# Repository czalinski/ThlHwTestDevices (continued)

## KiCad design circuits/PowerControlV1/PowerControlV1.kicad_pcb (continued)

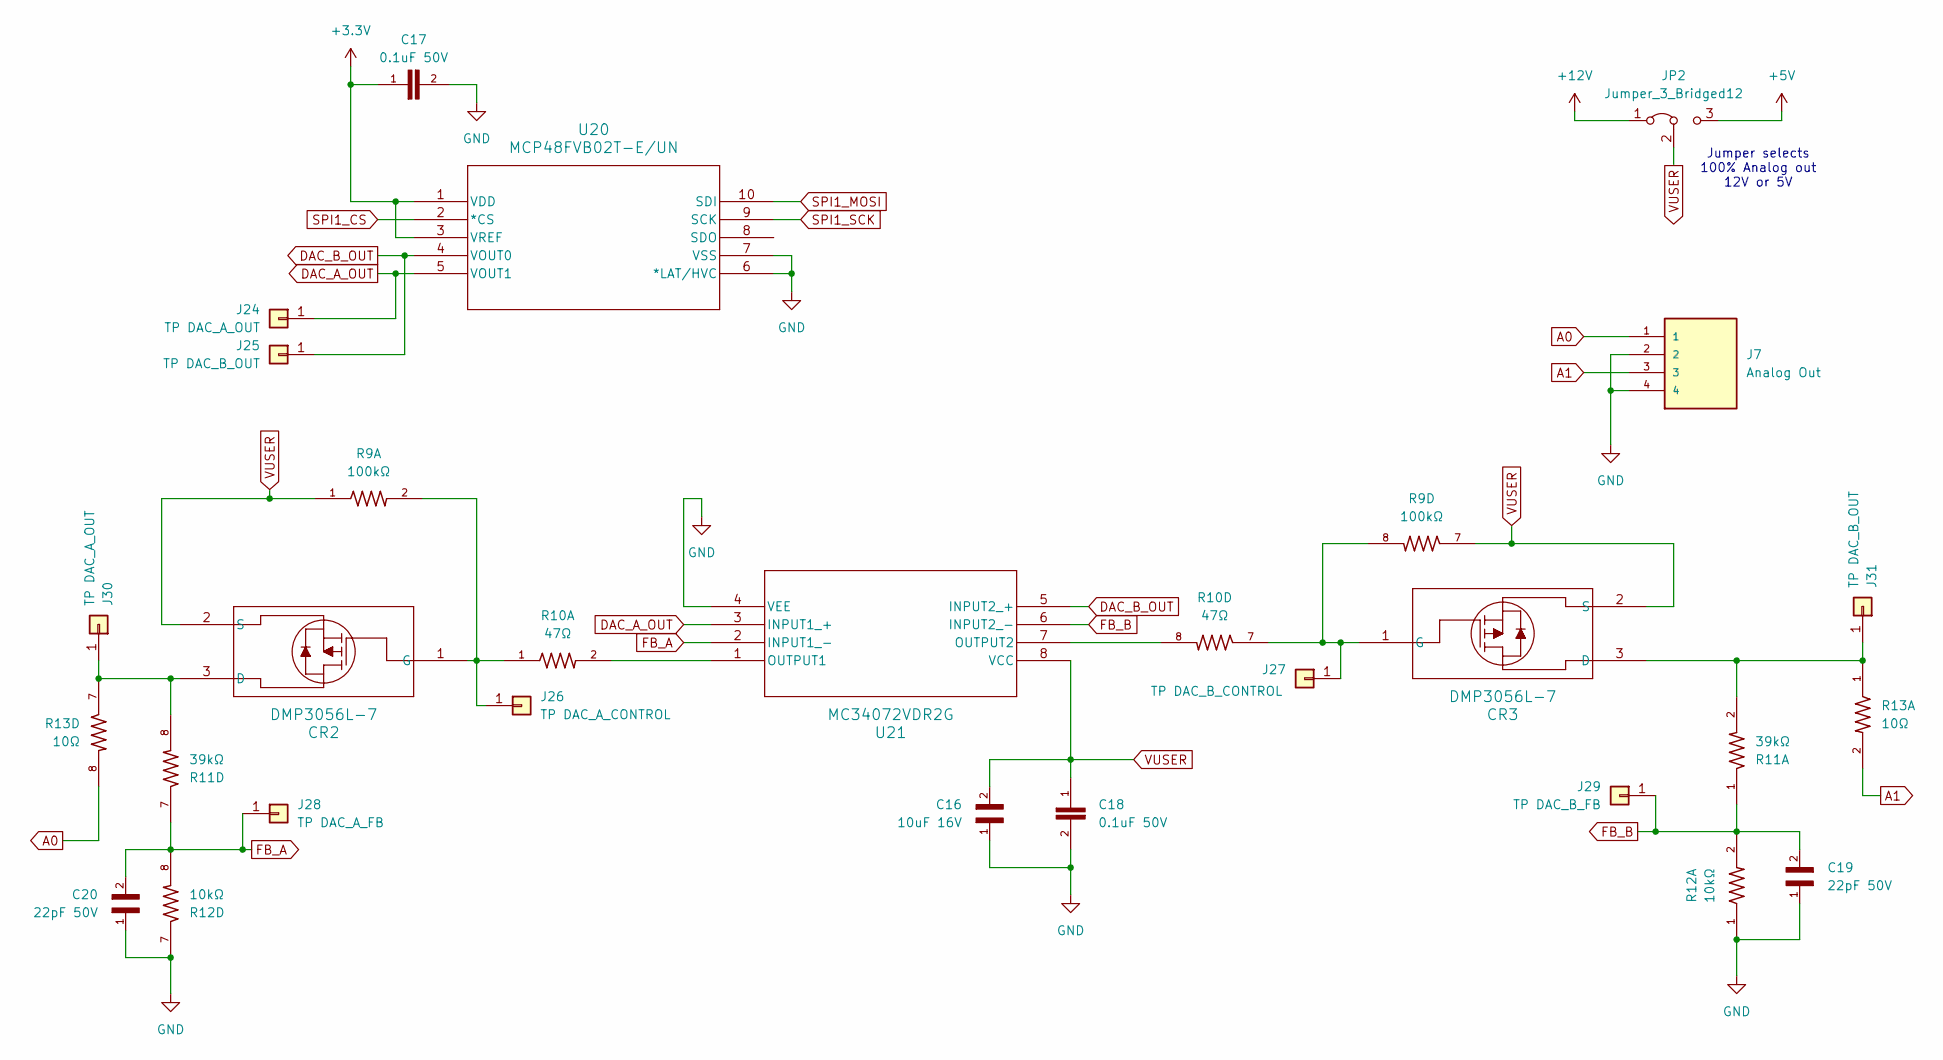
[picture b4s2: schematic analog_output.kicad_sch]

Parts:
C16: 10uF 16V; CAPC2012X140N
C17, C18: 0.1uF 50V; CAPC2012X70
C19, C20: 22pF 50V; CAPC1005X55N
CR2, CR3: DMP3056L-7; DIODE3_DESD1CAN2SOQ-7_DIO
J7: Analog Out; TE_1985218; PARTREV 29.03.2021
J24, J30: TP DAC_A_OUT; PinHeader_1x01_P2.54mm_Vertical
J25, J31: TP DAC_B_OUT; PinHeader_1x01_P2.54mm_Vertical
J26: TP DAC_A_CONTROL; PinHeader_1x01_P2.54mm_Vertical
J27: TP DAC_B_CONTROL; PinHeader_1x01_P2.54mm_Vertical
J28: TP DAC_A_FB; PinHeader_1x01_P2.54mm_Vertical
J29: TP DAC_B_FB; PinHeader_1x01_P2.54mm_Vertical
JP2: Jumper_3_Bridged12; PinHeader_1x03_P2.54mm_Vertical
R9: 100kΩ; RESCAV80P320X160X70-8N
R10: 47Ω; RESCAV80P320X160X70-8N
R11: 39kΩ; RESCAV80P320X160X70-8N
R12: 10kΩ; RESCAV80P320X160X70-8N
R13: 10Ω; RESCAV80P320X160X70-8N
U20: MCP48FVB02T-E/UN; MSOP10_UN_MCH
U21: MC34072VDR2G; SOIC8_ONS

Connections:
+3.3V: C17.1, U20.1 (VDD), U20.3 (VREF); also elsewhere on the board
+5V: JP2.3 (B); also elsewhere on the board
+12V: JP2.1 (A); also elsewhere on the board
A0: J7.1, R13.8
A1: J7.3, R13.2
DAC_A_OUT: J24.1, U20.5 (VOUT1), U21.3 (INPUT1_+)
DAC_B_OUT: J25.1, U20.4 (VOUT0), U21.5 (INPUT2_+)
FB_A: C20.2, J28.1, R11.7, R12.8, U21.2 (INPUT1_-)
FB_B: C19.2, J29.1, R11.1, R12.2, U21.6 (INPUT2_-)
GND: C16.1, C17.2, C18.2, C19.1, C20.1, J7.2, J7.4, R12.1, R12.7, U20.6 (*LAT/HVC), U20.7 (VSS), U21.4 (VEE); also elsewhere on the board
unnamed: CR2.3 (D), J30.1, R11.8, R13.7
unnamed: CR2.1 (G), J26.1, R9.2, R10.1
unnamed: CR3.3 (D), J31.1, R11.2, R13.1
unnamed: CR3.1 (G), J27.1, R9.8, R10.7
unnamed: R10.2, U21.1 (OUTPUT1)
unnamed: R10.8, U21.7 (OUTPUT2)
SPI1_CS: U20.2 (*CS); also elsewhere on the board
SPI1_MOSI: U20.10 (SDI); also elsewhere on the board
SPI1_SCK: U20.9 (SCK); also elsewhere on the board
VUSER: C16.2, C18.1, CR2.2 (S), CR3.2 (S), JP2.2 (C), R9.1, R9.7, U21.8 (VCC)

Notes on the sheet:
Jumper selects 100% Analog out 12V or 5V

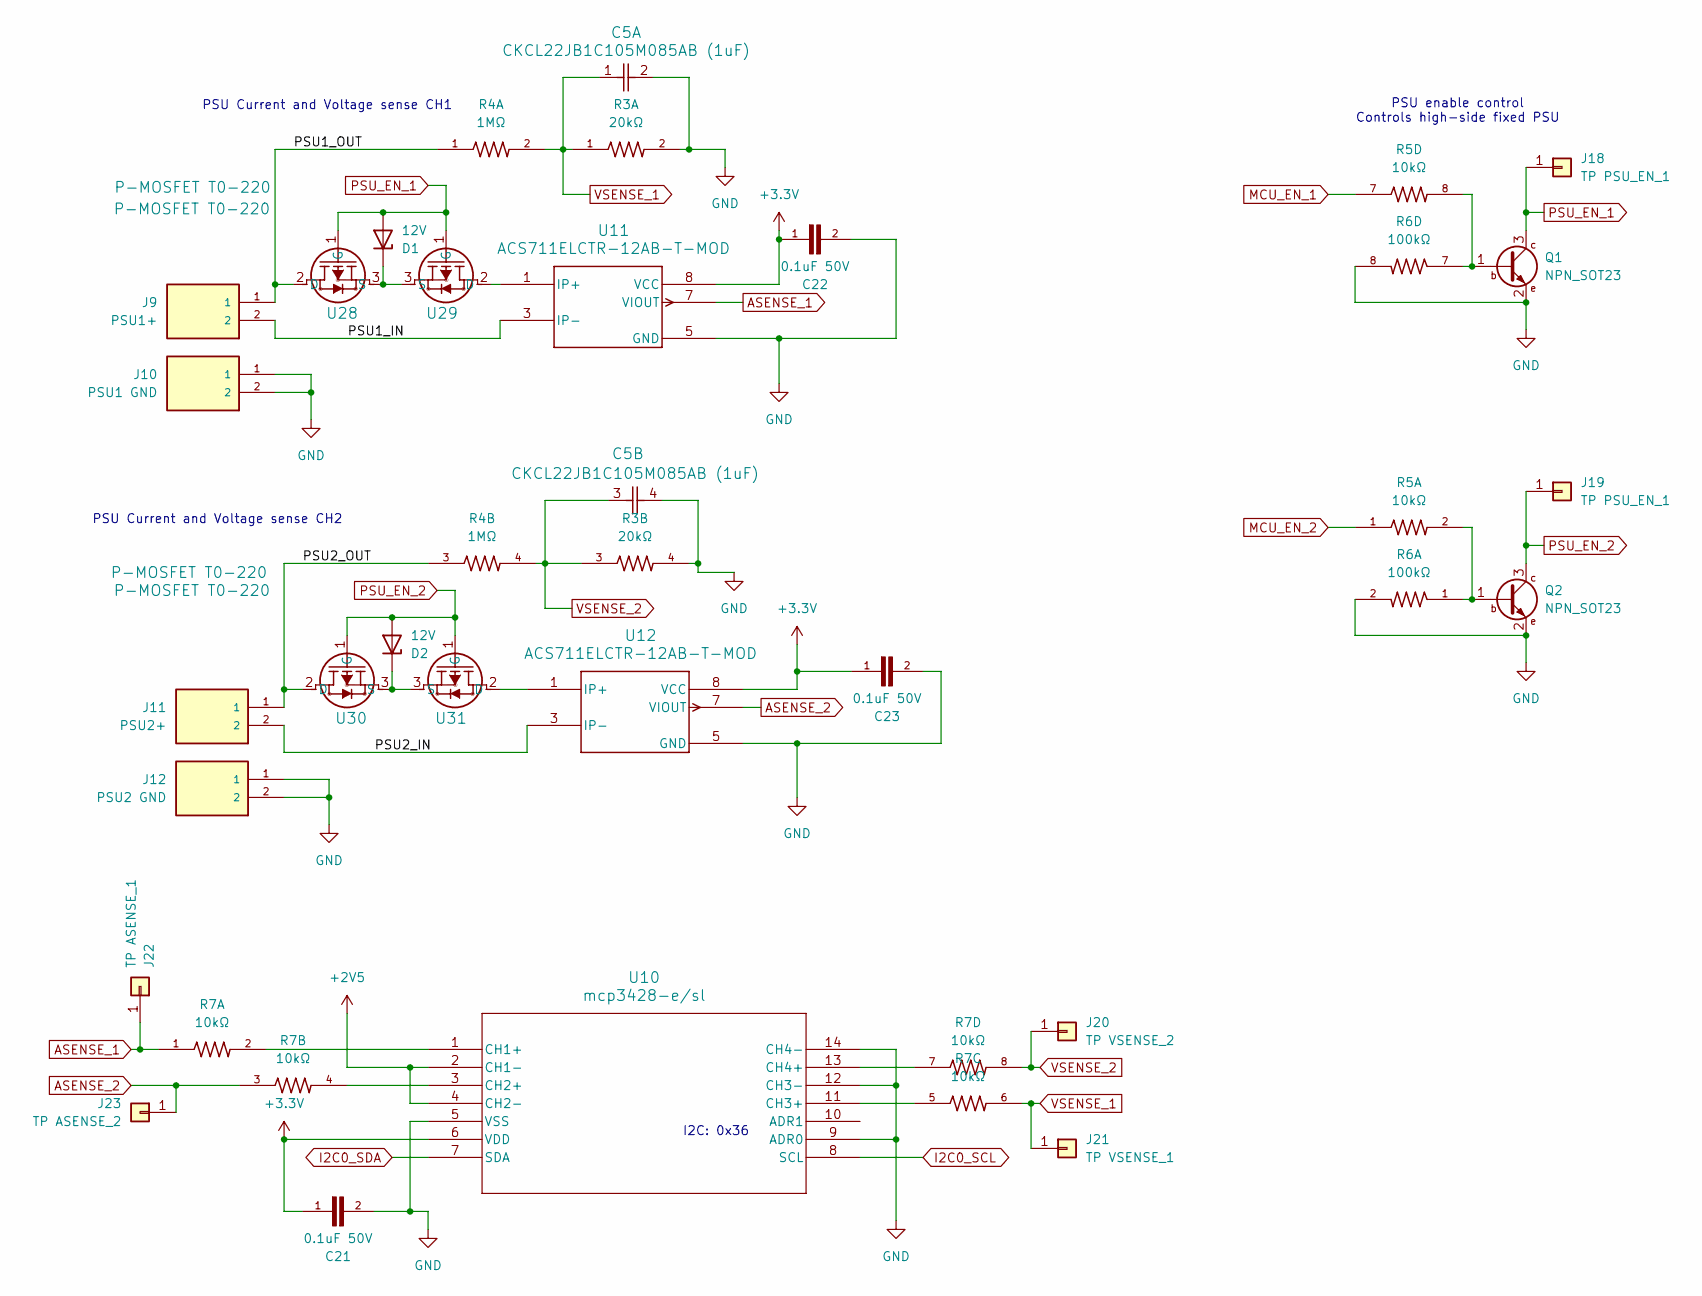
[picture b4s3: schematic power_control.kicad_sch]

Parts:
C5: CKCL22JB1C105M085AB (1uF); CAP_CKCL22_TDK
C21, C22, C23: 0.1uF 50V; CAPC2012X70
D1, D2: 12V; SOD-523_0P9X1P3_ONS
J9: PSU1+; CUI_TB005-762-02BE
J10: PSU1 GND; CUI_TB005-762-02BE
J11: PSU2+; CUI_TB005-762-02BE
J12: PSU2 GND; CUI_TB005-762-02BE
J18, J19: TP PSU_EN_1; PinHeader_1x01_P2.54mm_Vertical
J20: TP VSENSE_2; PinHeader_1x01_P2.54mm_Vertical
J21: TP VSENSE_1; PinHeader_1x01_P2.54mm_Vertical
J22: TP ASENSE_1; PinHeader_1x01_P2.54mm_Vertical
J23: TP ASENSE_2; PinHeader_1x01_P2.54mm_Vertical
Q1, Q2: NPN_SOT23; SOT-23_ONS-L
R3: 20kΩ; RESCAV80P320X160X70-8N
R4: 1MΩ; RESCAV80P320X160X70-8N
R5, R7: 10kΩ; RESCAV80P320X160X70-8N
R6: 100kΩ; RESCAV80P320X160X70-8N
U10: mcp3428-e/sl; SOIC14-N_MC_MCH
U11, U12: ACS711ELCTR-12AB-T-MOD; SOICN-8_ALM_MOD
U28, U29, U30, U31: P-MOSFET T0-220; TO220AB_VIS

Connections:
+2V5: U10.2 (CH1-), U10.4 (CH2-); also elsewhere on the board
+3.3V: C21.1, C22.1, C23.1, U10.6 (VDD), U11.8 (VCC), U12.8 (VCC); also elsewhere on the board
/PowerControl/PSU1_IN: J9.2, U11.3 (IP-)
/PowerControl/PSU1_OUT: J9.1, R4.1, U28.2 (D)
/PowerControl/PSU2_IN: J11.2, U12.3 (IP-)
/PowerControl/PSU2_OUT: J11.1, R4.3, U30.2 (D)
ASENSE_1: J22.1, R7.1, U11.7 (VIOUT)
ASENSE_2: J23.1, R7.3, U12.7 (VIOUT)
GND: C5.2, C5.4, C21.2, C22.2, C23.2, J10.1, J10.2, J12.1, J12.2, Q1.2 (E), Q2.2 (E), R3.2, R3.4, R6.2, R6.8, U10.5 (VSS), U10.9 (ADR0), U10.12 (CH3-), U10.14 (CH4-), U11.5 (GND), U12.5 (GND); also elsewhere on the board
I2C0_SCL: U10.8 (SCL); also elsewhere on the board
I2C0_SDA: U10.7 (SDA); also elsewhere on the board
MCU_EN_1: R5.7; also elsewhere on the board
MCU_EN_2: R5.1; also elsewhere on the board
unnamed: D1.1 (K), U28.3 (S), U29.3 (S)
unnamed: D2.1 (K), U30.3 (S), U31.3 (S)
unnamed: Q1.1 (B), R5.8, R6.7
unnamed: Q2.1 (B), R5.2, R6.1
unnamed: R7.2, U10.1 (CH1+)
unnamed: R7.4, U10.3 (CH2+)
unnamed: R7.5, U10.11 (CH3+)
unnamed: R7.7, U10.13 (CH4+)
unnamed: U11.1 (IP+), U29.2 (D)
unnamed: U12.1 (IP+), U31.2 (D)
PSU_EN_1: D1.2 (A), J18.1, Q1.3 (C), U28.1 (G), U29.1 (G)
PSU_EN_2: D2.2 (A), J19.1, Q2.3 (C), U30.1 (G), U31.1 (G)
VSENSE_1: C5.1, J21.1, R3.1, R4.2, R7.6
VSENSE_2: C5.3, J20.1, R3.3, R4.4, R7.8

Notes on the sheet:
PSU Current and Voltage sense CH1
I2C: 0x36
PSU enable control Controls high-side fixed PSU
PSU Current and Voltage sense CH2

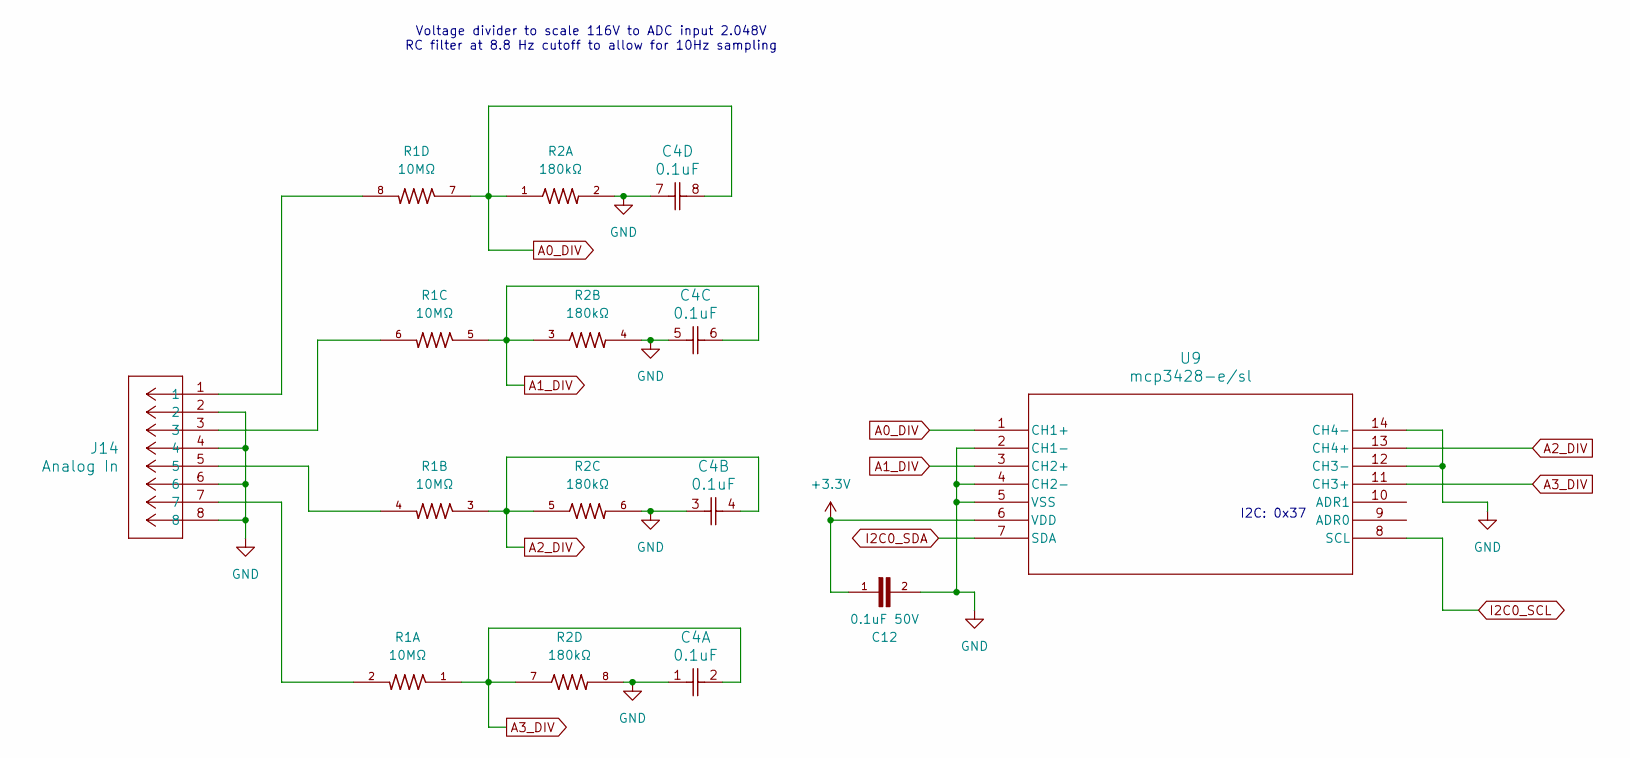
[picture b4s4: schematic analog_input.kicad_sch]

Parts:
C4: 0.1uF; CAP_CA0612_3P2X1P6_YAG
C12: 0.1uF 50V; CAPC2012X70
J14: Analog In; CONN_1989803_PXC
R1: 10MΩ; RESCAV80P320X160X70-8N
R2: 180kΩ; RESCAV80P320X160X70-8N
U9: mcp3428-e/sl; SOIC14-N_MC_MCH

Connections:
+3.3V: C12.1, U9.6 (VDD); also elsewhere on the board
A0_DIV: C4.8, R1.7, R2.1, U9.1 (CH1+)
A1_DIV: C4.6, R1.5, R2.3, U9.3 (CH2+)
A2_DIV: C4.4, R1.3, R2.5, U9.13 (CH4+)
A3_DIV: C4.2, R1.1, R2.7, U9.11 (CH3+)
GND: C4.1, C4.3, C4.5, C4.7, C12.2, J14.2, J14.4, J14.6, J14.8, R2.2, R2.4, R2.6, R2.8, U9.2 (CH1-), U9.4 (CH2-), U9.5 (VSS), U9.12 (CH3-), U9.14 (CH4-); also elsewhere on the board
I2C0_SCL: U9.8 (SCL); also elsewhere on the board
I2C0_SDA: U9.7 (SDA); also elsewhere on the board
unnamed: J14.1, R1.8
unnamed: J14.3, R1.6
unnamed: J14.5, R1.4
unnamed: J14.7, R1.2

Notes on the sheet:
Voltage divider to scale 116V to ADC input 2.048V RC filter at 8.8 Hz cutoff to allow for 10Hz sampling
I2C: 0x37

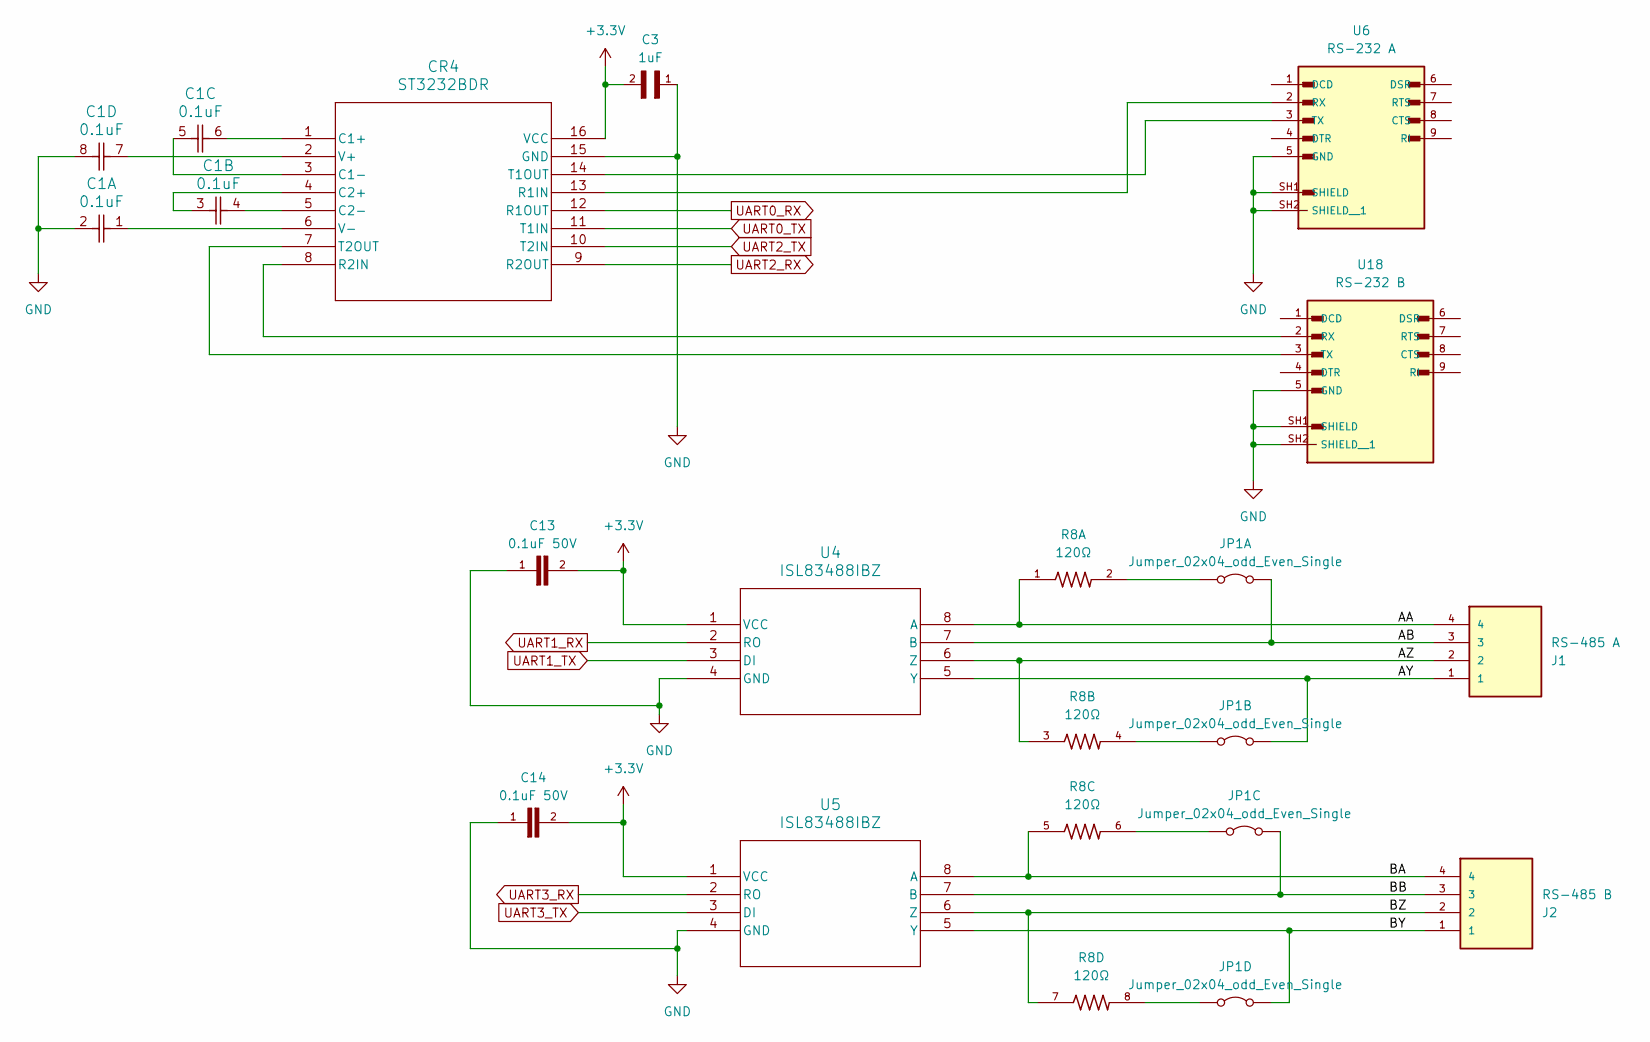
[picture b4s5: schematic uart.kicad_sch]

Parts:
C1: 0.1uF; CAP_CA0612_3P2X1P6_YAG
C3: 1uF; CAPC1608X90N
C13, C14: 0.1uF 50V; CAPC2012X70
CR4: ST3232BDR; SO-16_STM
J1: RS-485 A; TE_1985218; PARTREV 29.03.2021
J2: RS-485 B; TE_1985218; PARTREV 29.03.2021
JP1: Jumper_02x04_odd_Even_Single; PinHeader_2x04_P2.54mm_Vertical
R8: 120Ω; RESCAV80P320X160X70-8N
U4, U5: ISL83488IBZ; SOIC8_4X5_INR
U6: RS-232 A; ASSMANN_A-DS_09_A_KG-T2S
U18: RS-232 B; ASSMANN_A-DS_09_A_KG-T2S

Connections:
+3.3V: C3.2, C13.2, C14.2, CR4.16 (VCC), U4.1 (VCC), U5.1 (VCC); also elsewhere on the board
/UART/AA: J1.4, R8.1, U4.8 (A)
/UART/AB: J1.3, JP1.2 (B), U4.7 (B)
/UART/AY: J1.1, JP1.4 (B), U4.5 (Y)
/UART/AZ: J1.2, R8.3, U4.6 (Z)
/UART/BA: J2.4, R8.5, U5.8 (A)
/UART/BB: J2.3, JP1.6 (B), U5.7 (B)
/UART/BY: J2.1, JP1.8 (B), U5.5 (Y)
/UART/BZ: J2.2, R8.7, U5.6 (Z)
GND: C1.2, C1.8, C3.1, C13.1, C14.1, CR4.15 (GND), U4.4 (GND), U5.4 (GND), U6.5 (GND), U6.SH1 (SHIELD), U6.SH2 (SHIELD__1), U18.5 (GND), U18.SH1 (SHIELD), U18.SH2 (SHIELD__1); also elsewhere on the board
unnamed: C1.6, CR4.1 (C1+)
unnamed: C1.5, CR4.3 (C1-)
unnamed: C1.3, CR4.4 (C2+)
unnamed: C1.4, CR4.5 (C2-)
unnamed: CR4.13 (R1IN), U6.2 (RX)
unnamed: CR4.8 (R2IN), U18.2 (RX)
unnamed: CR4.14 (T1OUT), U6.3 (TX)
unnamed: CR4.7 (T2OUT), U18.3 (TX)
unnamed: C1.7, CR4.2 (V+)
unnamed: C1.1, CR4.6 (V-)
unnamed: JP1.1 (A), R8.2
unnamed: JP1.3 (A), R8.4
unnamed: JP1.5 (A), R8.6
unnamed: JP1.7 (A), R8.8
UART0_RX: CR4.12 (R1OUT); also elsewhere on the board
UART0_TX: CR4.11 (T1IN); also elsewhere on the board
UART1_RX: U4.2 (RO); also elsewhere on the board
UART1_TX: U4.3 (DI); also elsewhere on the board
UART2_RX: CR4.9 (R2OUT); also elsewhere on the board
UART2_TX: CR4.10 (T2IN); also elsewhere on the board
UART3_RX: U5.2 (RO); also elsewhere on the board
UART3_TX: U5.3 (DI); also elsewhere on the board

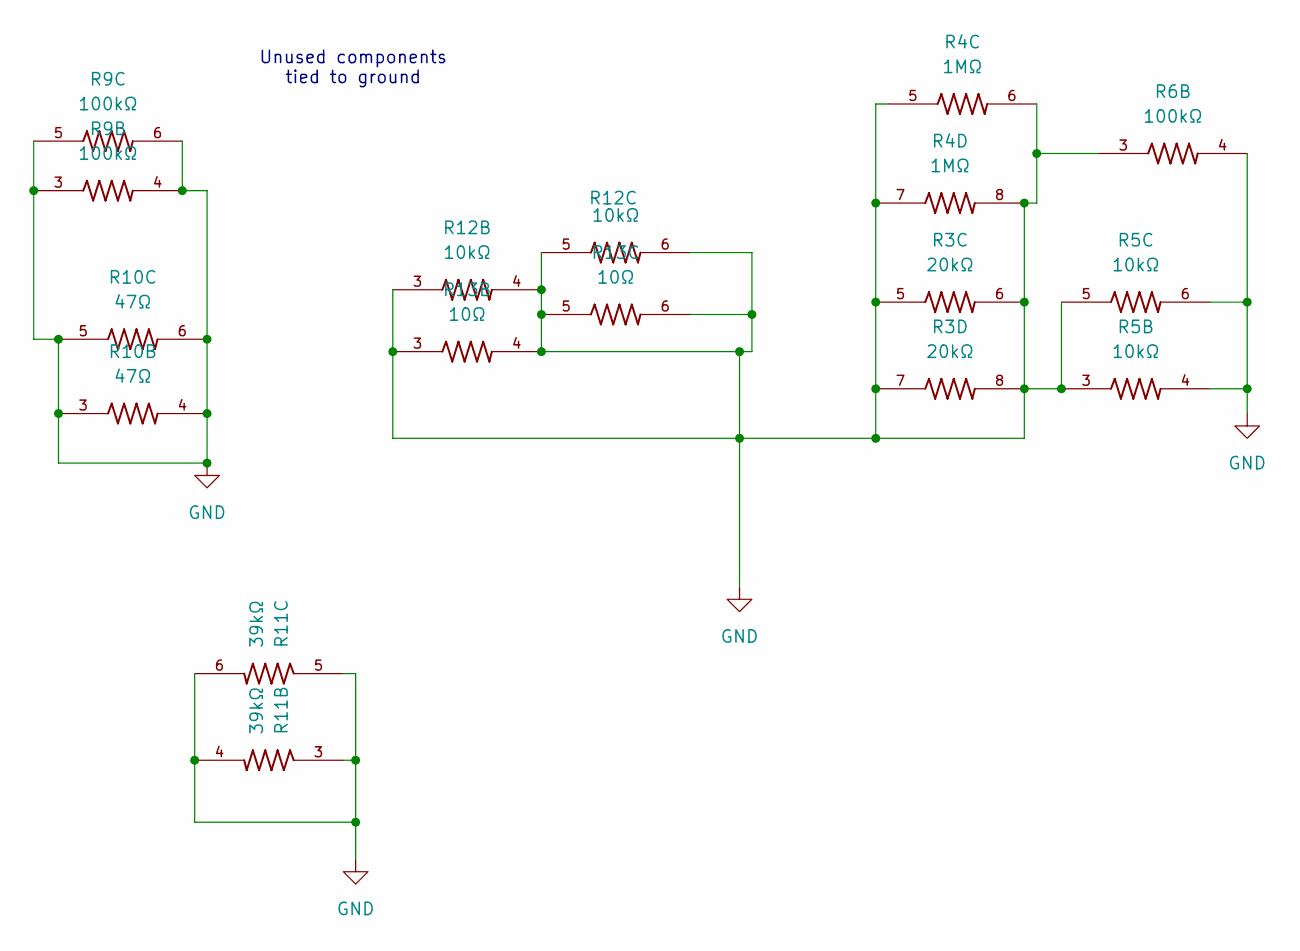
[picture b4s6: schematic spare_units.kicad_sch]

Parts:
R3: 20kΩ; RESCAV80P320X160X70-8N
R4: 1MΩ; RESCAV80P320X160X70-8N
R5, R12: 10kΩ; RESCAV80P320X160X70-8N
R6, R9: 100kΩ; RESCAV80P320X160X70-8N
R10: 47Ω; RESCAV80P320X160X70-8N
R11: 39kΩ; RESCAV80P320X160X70-8N
R13: 10Ω; RESCAV80P320X160X70-8N

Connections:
GND: R3.5, R3.6, R3.7, R3.8, R4.5, R4.6, R4.7, R4.8, R5.3, R5.4, R5.5, R5.6, R6.3, R6.4, R9.3, R9.4, R9.5, R9.6, R10.3, R10.4, R10.5, R10.6, R11.3, R11.4, R11.5, R11.6, R12.3, R12.4, R12.5, R12.6, R13.3, R13.4, R13.5, R13.6; also elsewhere on the board

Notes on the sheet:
Unused components tied to ground

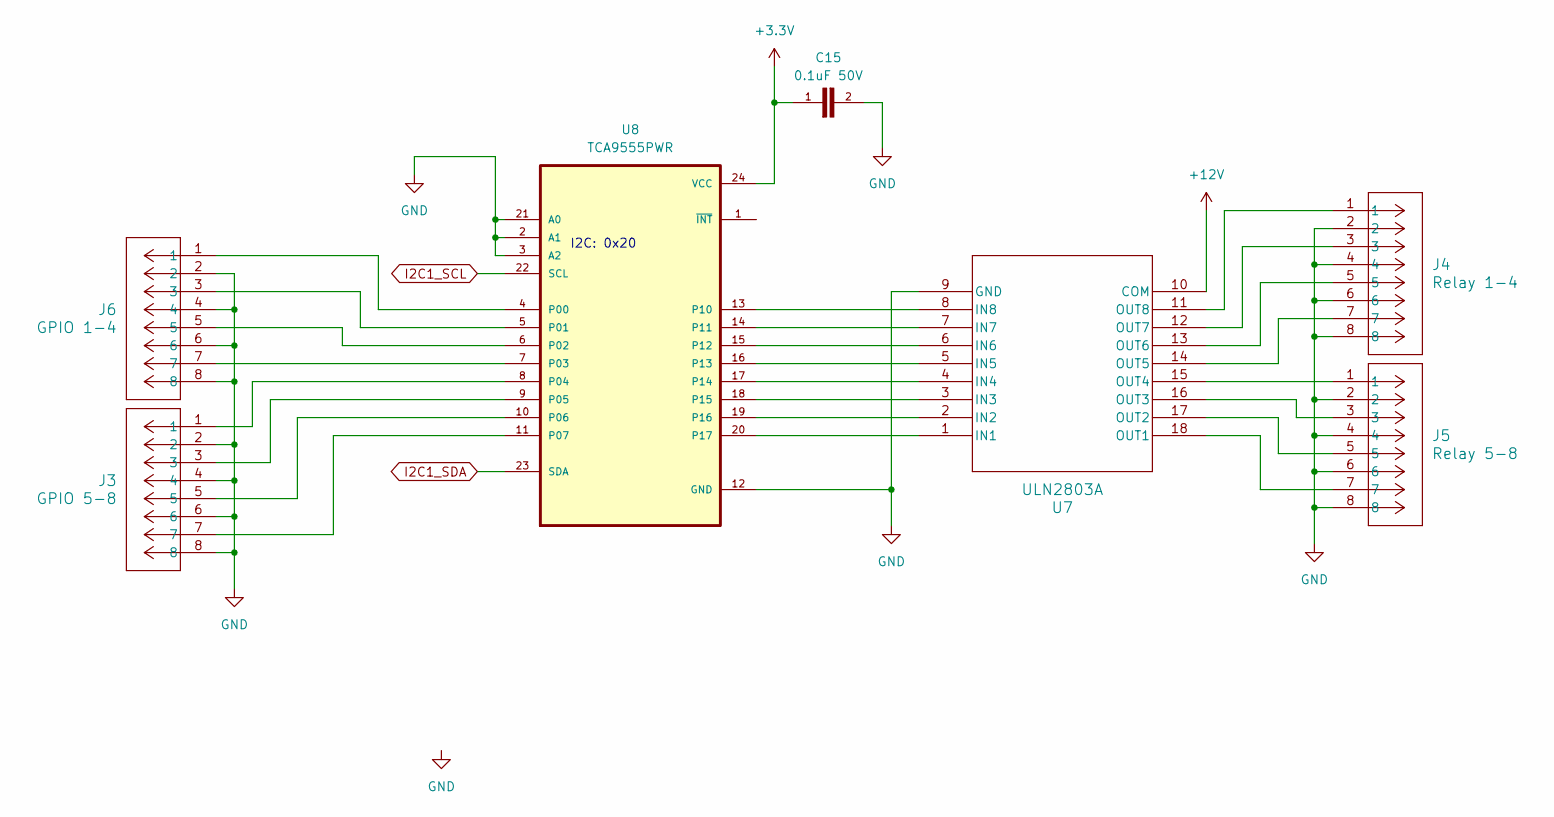
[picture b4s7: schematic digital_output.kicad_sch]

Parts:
C15: 0.1uF 50V; CAPC2012X70
J3: GPIO 5-8; CONN_1989803_PXC
J4: Relay 1-4; CONN_1989803_PXC
J5: Relay 5-8; CONN_1989803_PXC
J6: GPIO 1-4; CONN_1989803_PXC
U7: ULN2803A; DIP-18_STM
U8: TCA9555PWR; SOP65P640X120-24N

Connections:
+3.3V: C15.1, U8.24 (VCC); also elsewhere on the board
+12V: U7.10 (COM); also elsewhere on the board
GND: C15.2, J3.2, J3.4, J3.6, J3.8, J4.2, J4.4, J4.6, J4.8, J5.2, J5.4, J5.6, J5.8, J6.2, J6.4, J6.6, J6.8, U7.9 (GND), U8.2 (A1), U8.3 (A2), U8.12 (GND), U8.21 (A0); also elsewhere on the board
I2C1_SCL: U8.22 (SCL); also elsewhere on the board
I2C1_SDA: U8.23 (SDA); also elsewhere on the board
unnamed: U7.1 (IN1), U8.20 (P17)
unnamed: U7.2 (IN2), U8.19 (P16)
unnamed: U7.3 (IN3), U8.18 (P15)
unnamed: U7.4 (IN4), U8.17 (P14)
unnamed: U7.5 (IN5), U8.16 (P13)
unnamed: U7.6 (IN6), U8.15 (P12)
unnamed: U7.7 (IN7), U8.14 (P11)
unnamed: U7.8 (IN8), U8.13 (P10)
unnamed: J5.7, U7.18 (OUT1)
unnamed: J5.5, U7.17 (OUT2)
unnamed: J5.3, U7.16 (OUT3)
unnamed: J5.1, U7.15 (OUT4)
unnamed: J4.7, U7.14 (OUT5)
unnamed: J4.5, U7.13 (OUT6)
unnamed: J4.3, U7.12 (OUT7)
unnamed: J4.1, U7.11 (OUT8)
unnamed: J6.1, U8.4 (P00)
unnamed: J6.3, U8.5 (P01)
unnamed: J6.5, U8.6 (P02)
unnamed: J6.7, U8.7 (P03)
unnamed: J3.1, U8.8 (P04)
unnamed: J3.3, U8.9 (P05)
unnamed: J3.5, U8.10 (P06)
unnamed: J3.7, U8.11 (P07)

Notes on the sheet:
I2C: 0x20

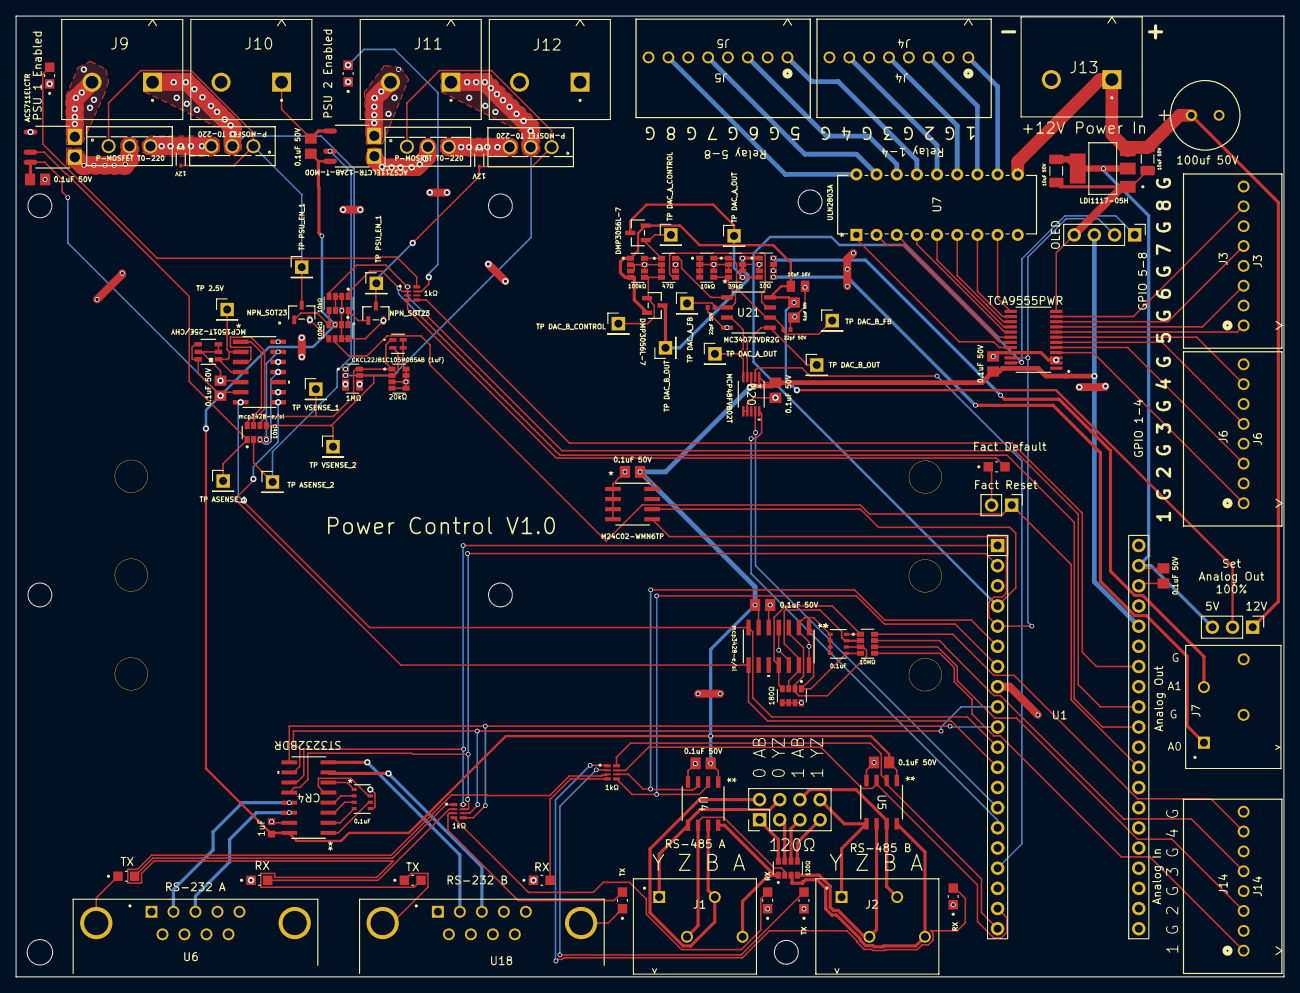
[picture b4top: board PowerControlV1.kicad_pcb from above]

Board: 2 copper layers, 159.7 x 121.0 mm, 107 parts (0 on the bottom side), 122 nets.

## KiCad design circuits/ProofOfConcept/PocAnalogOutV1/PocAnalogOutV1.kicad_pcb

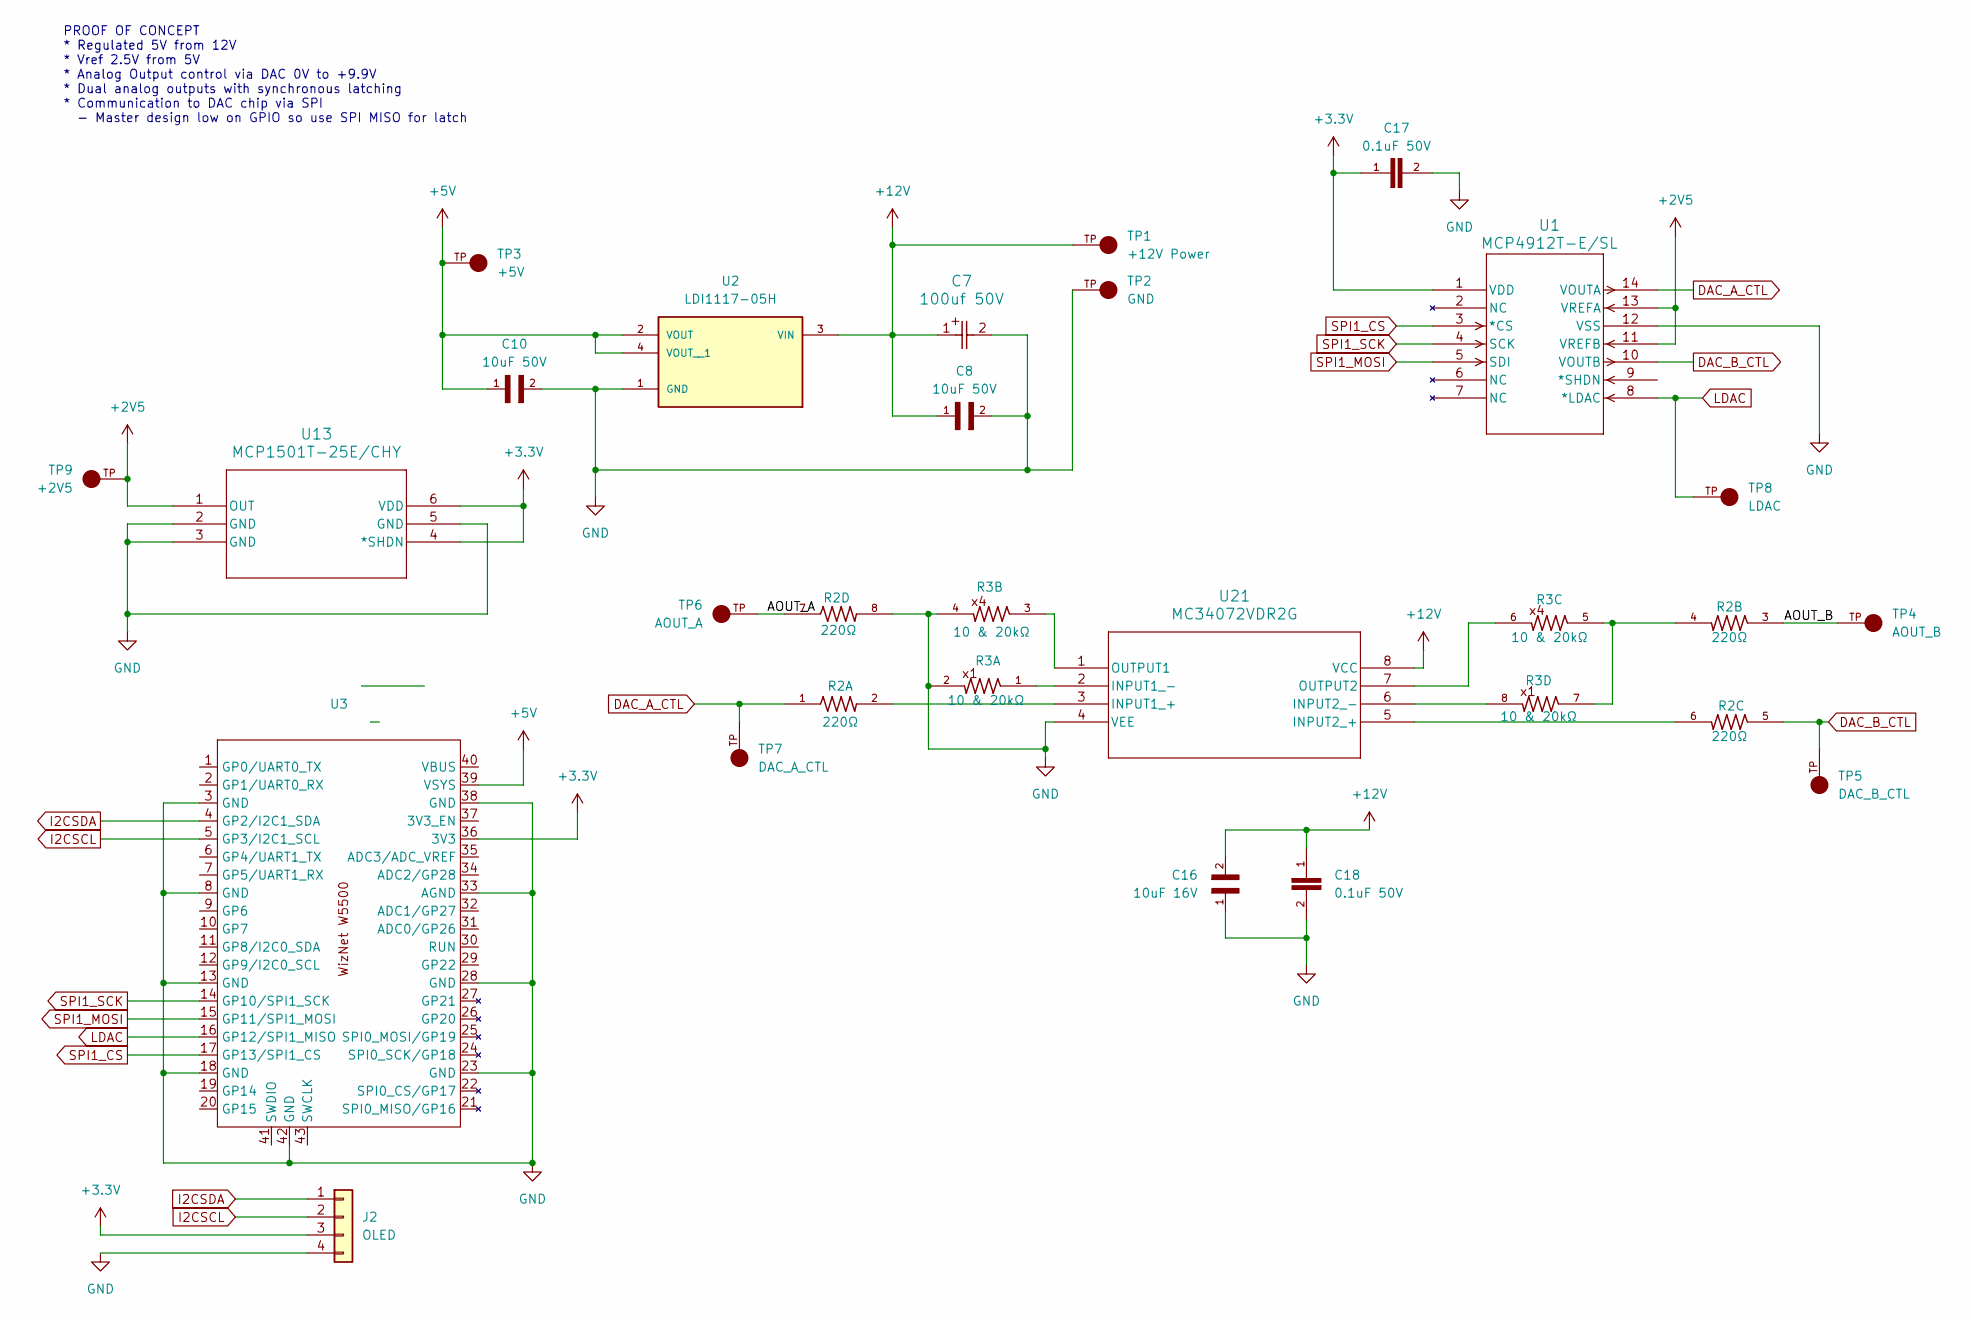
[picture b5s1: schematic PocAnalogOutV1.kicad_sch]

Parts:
C7: 100uf 50V; CAP_YX_8X11P5_RUB
C8, C10: 10uF 50V; CAPC3216X180N
C16: 10uF 16V; CAPC2012X140N
C17, C18: 0.1uF 50V; CAPC2012X70
J2: OLED; PinHeader_1x04_P2.54mm_Vertical
R2: 220Ω; RESCAV80P320X160X70-8N
R3: 10 & 20kΩ; RESCAV80P320X160X70-8N
TP1: +12V Power; KEYSTONE_4954_Slot; PARTREV B; DigiKey_Part_Number 36-4954-ND
TP2: GND; KEYSTONE_4954_Slot; PARTREV B; DigiKey_Part_Number 36-4954-ND
TP3: +5V; KEYSTONE_4954_Slot; PARTREV B; DigiKey_Part_Number 36-4954-ND
TP4: AOUT_B; KEYSTONE_4954_Slot; PARTREV B; DigiKey_Part_Number 36-4954-ND
TP5: DAC_B_CTL; KEYSTONE_4954_Slot; PARTREV B; DigiKey_Part_Number 36-4954-ND
TP6: AOUT_A; KEYSTONE_4954_Slot; PARTREV B; DigiKey_Part_Number 36-4954-ND
TP7: DAC_A_CTL; KEYSTONE_4954_Slot; PARTREV B; DigiKey_Part_Number 36-4954-ND
TP8: LDAC; KEYSTONE_4954_Slot; PARTREV B; DigiKey_Part_Number 36-4954-ND
TP9: +2V5; KEYSTONE_4954_Slot; PARTREV B; DigiKey_Part_Number 36-4954-ND
U1: MCP4912T-E/SL; SOIC14-N_MC_MCH
U2: LDI1117-05H; SOT230P700X165-4N; PARTREV 2023-02-01
U3: WizNetPico_OnBoard
U13: MCP1501T-25E/CHY; SOT-23_OT&slash_OTY_MCH
U21: MC34072VDR2G; SOIC8_ONS

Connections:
+2V5: TP9.TP, U1.11 (VREFB), U1.13 (VREFA), U13.1 (OUT)
+3.3V: C17.1, J2.3, U1.1 (VDD), U3.36 (3V3), U13.4 (*SHDN), U13.6 (VDD)
+5V: C10.1, TP3.TP, U2.2 (VOUT), U2.4 (VOUT__1), U3.39 (VSYS)
+12V: C7.1, C8.1, C16.2, C18.1, TP1.TP, U2.3 (VIN), U21.8 (VCC)
/AOUT_A: R2.7, TP6.TP
/AOUT_B: R2.3, TP4.TP
DAC_A_CTL: R2.1, TP7.TP, U1.14 (VOUTA)
DAC_B_CTL: R2.5, TP5.TP, U1.10 (VOUTB)
GND: C7.2, C8.2, C10.2, C16.1, C17.2, C18.2, J2.4, R2.8, R3.2, R3.4, TP2.TP, U1.12 (VSS), U2.1 (GND), U3.3 (GND), U3.8 (GND), U3.13 (GND), U3.18 (GND), U3.23 (GND), U3.28 (GND), U3.33 (AGND), U3.38 (GND), U3.42 (GND), U13.2 (GND), U13.3 (GND), U13.5 (GND), U21.4 (VEE)
I2CSCL: J2.2, U3.5 (GP3/I2C1_SCL)
I2CSDA: J2.1, U3.4 (GP2/I2C1_SDA)
LDAC: TP8.TP, U1.8 (*LDAC), U3.16 (GP12/SPI1_MISO)
unnamed: R2.4, R3.5, R3.7
unnamed: R2.2, U21.3 (INPUT1_+)
unnamed: R3.1, U21.2 (INPUT1_-)
unnamed: R2.6, U21.5 (INPUT2_+)
unnamed: R3.8, U21.6 (INPUT2_-)
unnamed: R3.3, U21.1 (OUTPUT1)
unnamed: R3.6, U21.7 (OUTPUT2)
SPI1_CS: U1.3 (*CS), U3.17 (GP13/SPI1_CS)
SPI1_MOSI: U1.5 (SDI), U3.15 (GP11/SPI1_MOSI)
SPI1_SCK: U1.4 (SCK), U3.14 (GP10/SPI1_SCK)

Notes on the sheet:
PROOF OF CONCEPT * Regulated 5V from 12V * Vref 2.5V from 5V * Analog Output control via DAC 0V to +9.9V * Dual analog outputs with synchronous latching * Communication to DAC chip via SPI - Master design low on GPIO so use SPI MISO for latch

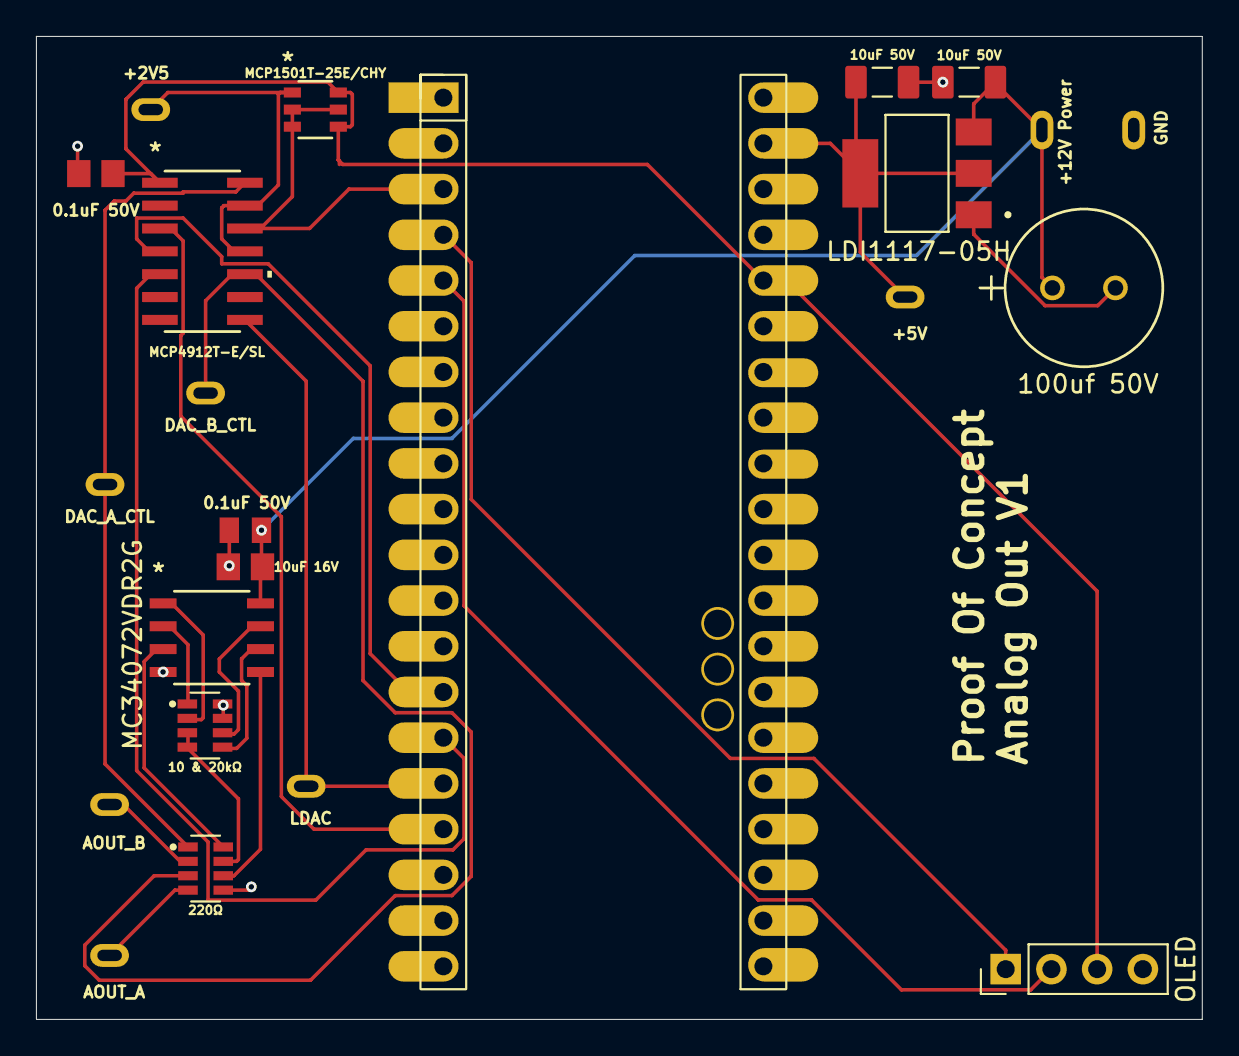
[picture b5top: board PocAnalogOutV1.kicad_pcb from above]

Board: 2 copper layers, 64.8 x 54.6 mm, 23 parts (0 on the bottom side), 22 nets.
